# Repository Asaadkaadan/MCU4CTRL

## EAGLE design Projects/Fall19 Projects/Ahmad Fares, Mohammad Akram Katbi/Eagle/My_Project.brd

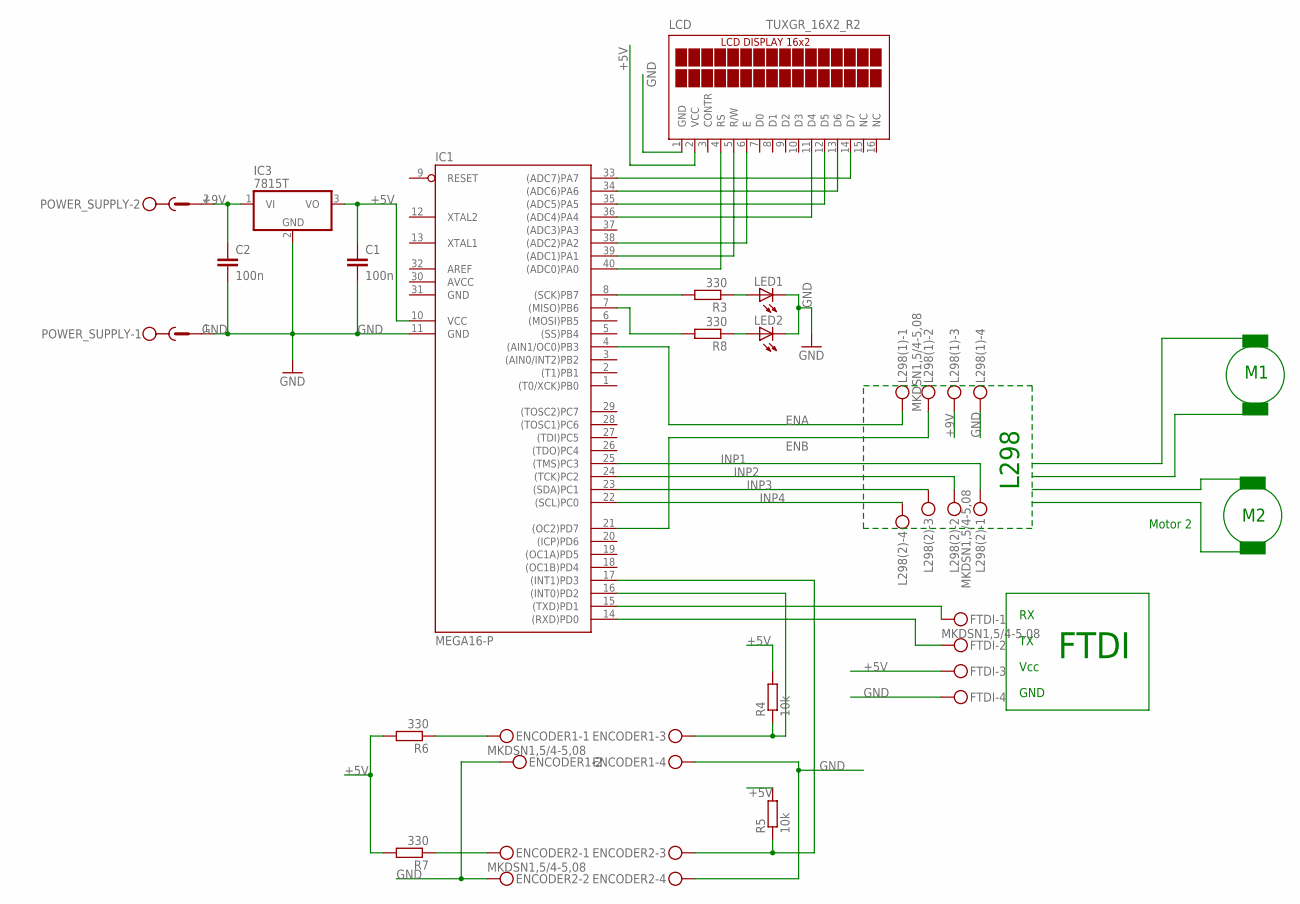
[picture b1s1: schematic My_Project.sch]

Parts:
C1, C2: 100n; C2.5-3
ENCODER1, ENCODER2: MKDSN1,5/4-5,08
FTDI: MKDSN1,5/4-5,08
IC1: MEGA16-P; DIL40; MPN ATMEGA16-16PU
IC3: 7815T; TO220H
L298(1), L298(2): MKDSN1,5/4-5,08
LCD: TUXGR_16X2_R2
LED1, LED2: LEDLZR181; LZR181
POWER_SUPPLY: MSTBV2
R3, R6, R7, R8: 330; 0207/10
R4, R5: 10k; 0207/10

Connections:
+5V: C1.1, FTDI.3, IC1.10 (VCC), IC3.3 (VO), LCD.2 (VCC), R4.2, R5.2, R6.2, R7.2
+9V: C2.1, IC3.1 (VI), L298(1).3, POWER_SUPPLY.2
AVCC: IC1.30 (AVCC)
ENA: IC1.4 ((AIN1/OC0)PB3), L298(1).1
ENB: IC1.21 ((OC2)PD7), L298(1).2
GND: C1.2, C2.2, ENCODER1.2, ENCODER1.4, ENCODER2.2, ENCODER2.4, FTDI.4, IC1.11 (GND), IC1.31 (GND), IC3.2 (GND), L298(1).4, LCD.1 (GND), LED1.K (C), LED2.K (C), POWER_SUPPLY.1
INP1: IC1.25 ((TMS)PC3), L298(2).1
INP2: IC1.24 ((TCK)PC2), L298(2).2
INP3: IC1.23 ((SDA)PC1), L298(2).3
INP4: IC1.22 ((SCL)PC0), L298(2).4
LCD(D4): IC1.36 ((ADC4)PA4), LCD.11 (D4)
LCD(D5): IC1.35 ((ADC5)PA5), LCD.12 (D5)
LCD(D6): IC1.34 ((ADC6)PA6), LCD.13 (D6)
LCD(D7): IC1.33 ((ADC7)PA7), LCD.14 (D7)
LCD(E): IC1.38 ((ADC2)PA2), LCD.6 (E)
LCD(RS): IC1.40 ((ADC0)PA0), LCD.4 (RS)
LCD(RW): IC1.39 ((ADC1)PA1), LCD.5 (R/W)
unnamed: IC1.7 ((MISO)PB6), R8.2
unnamed: IC1.8 ((SCK)PB7), R3.2
unnamed: LED1.A, R3.1
unnamed: LED2.A, R8.1
unnamed: ENCODER1.1, R6.1
unnamed: ENCODER1.3, IC1.16 ((INT0)PD2), R4.1
unnamed: ENCODER2.3, IC1.17 ((INT1)PD3), R5.1
unnamed: ENCODER2.1, R7.1
RX: FTDI.2, IC1.14 ((RXD)PD0)
TX: FTDI.1, IC1.15 ((TXD)PD1)

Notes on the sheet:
Vcc
GND
FTDI
Motor 2
L298

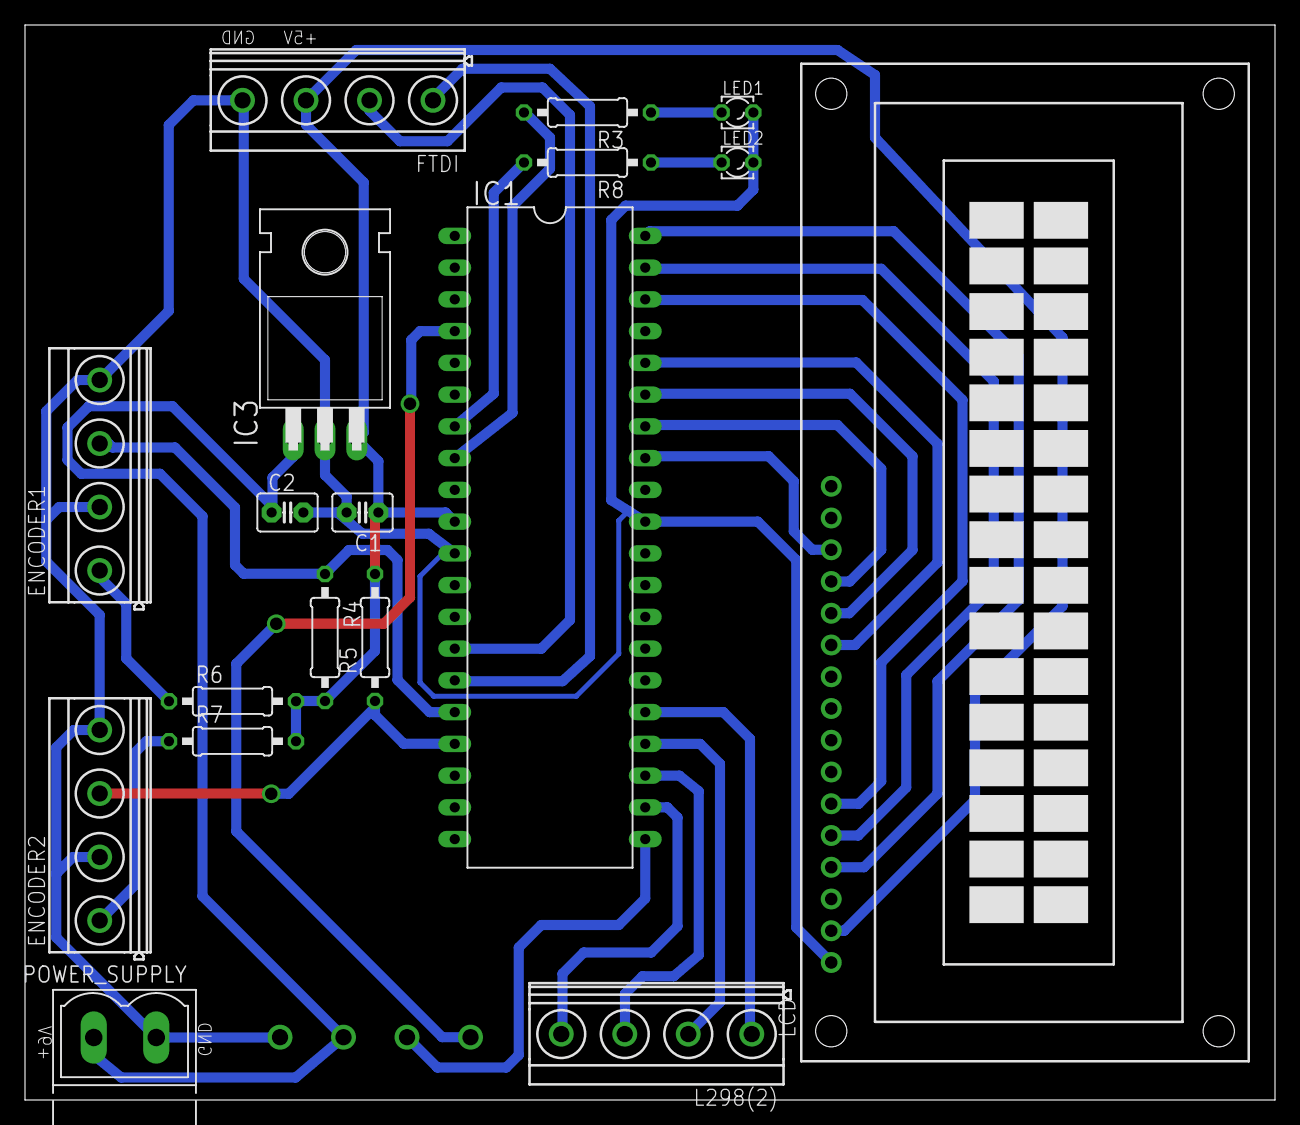
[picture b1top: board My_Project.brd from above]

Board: 2 copper layers, 100.0 x 86.0 mm, 19 parts (1 on the bottom side), 26 nets.

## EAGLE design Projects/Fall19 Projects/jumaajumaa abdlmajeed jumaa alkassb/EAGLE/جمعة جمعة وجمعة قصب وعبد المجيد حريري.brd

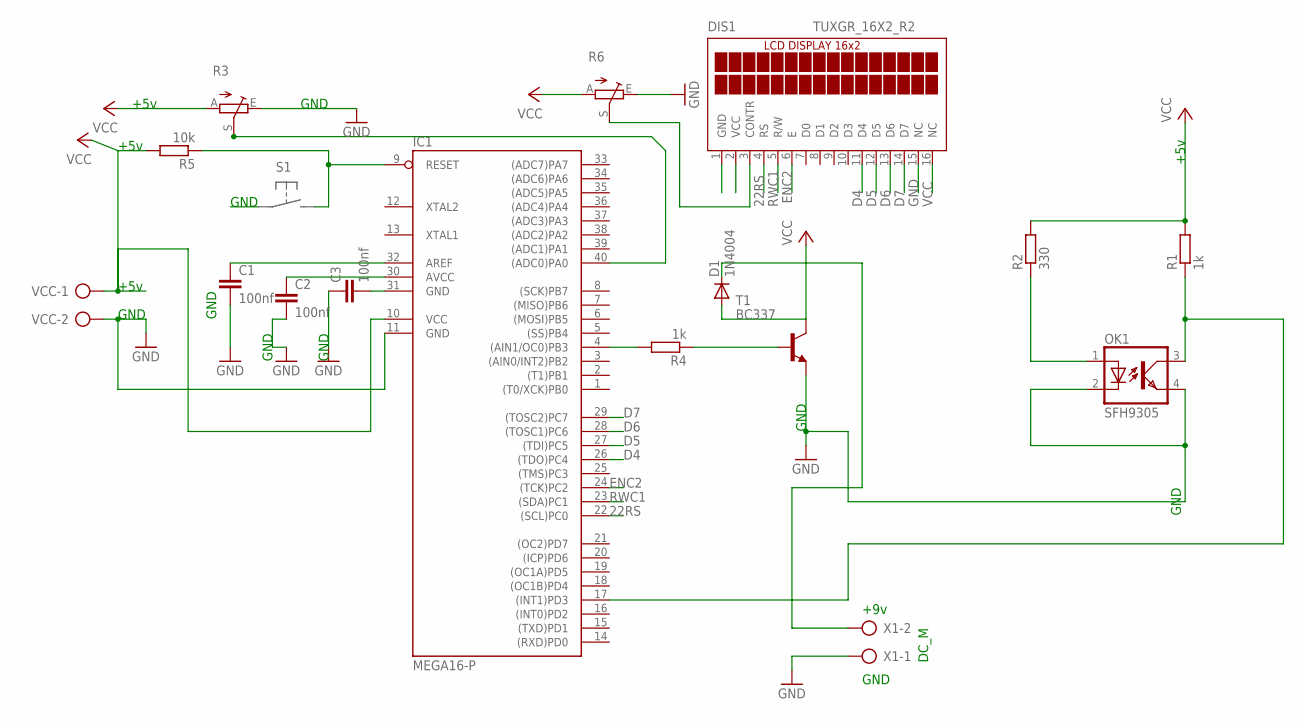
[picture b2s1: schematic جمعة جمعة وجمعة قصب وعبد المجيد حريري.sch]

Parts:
C1, C2, C3: 100nf; C2.5-3
D1: 1N4004; DO41-10
DIS1: TUXGR_16X2_R2
IC1: MEGA16-P; DIL40
OK1: SFH9305
R1, R4: 1k; 0204/7
R2: 330; 0204/7
R3, R6: TRIM_EU-CA9V; CA9V
R5: 10k; 0204/7
T1: BC337; TO92
VCC: AK300/2
X1: AK300/2

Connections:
22RS: DIS1.4 (RS), IC1.22 ((SCL)PC0)
D4: DIS1.11 (D4), IC1.26 ((TDO)PC4)
D5: DIS1.12 (D5), IC1.27 ((TDI)PC5)
D6: DIS1.13 (D6), IC1.28 ((TOSC1)PC6)
D7: DIS1.14 (D7), IC1.29 ((TOSC2)PC7)
ENC2: DIS1.6 (E), IC1.24 ((TCK)PC2)
GND: C1.2, C2.2, C3.1, DIS1.15 (NC), IC1.11 (GND), OK1.2 (C), OK1.4 (EMIT), R3.E, R6.E, T1.1 (E), VCC.2, X1.1
unnamed: OK1.1 (A), R2.1
unnamed: IC1.17 ((INT1)PD3), OK1.3 (COL), R1.1
unnamed: IC1.9 (RESET), R5.1
unnamed: C1.1, IC1.32 (AREF)
unnamed: R4.1, T1.2 (B)
unnamed: IC1.4 ((AIN1/OC0)PB3), R4.2
unnamed: C2.1, IC1.30 (AVCC)
unnamed: C3.2, IC1.31 (GND)
unnamed: IC1.40 ((ADC0)PA0), R3.S
unnamed: DIS1.3 (CONTR), R6.S
unnamed: D1.A, T1.3 (C)
RWC1: DIS1.5 (R/W), IC1.23 ((SDA)PC1)
VCC: D1.C, DIS1.16 (NC), IC1.10 (VCC), R1.2, R2.2, R3.A, R5.2, R6.A, VCC.1, X1.2

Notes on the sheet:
+5v
GND
DC_M
+9v

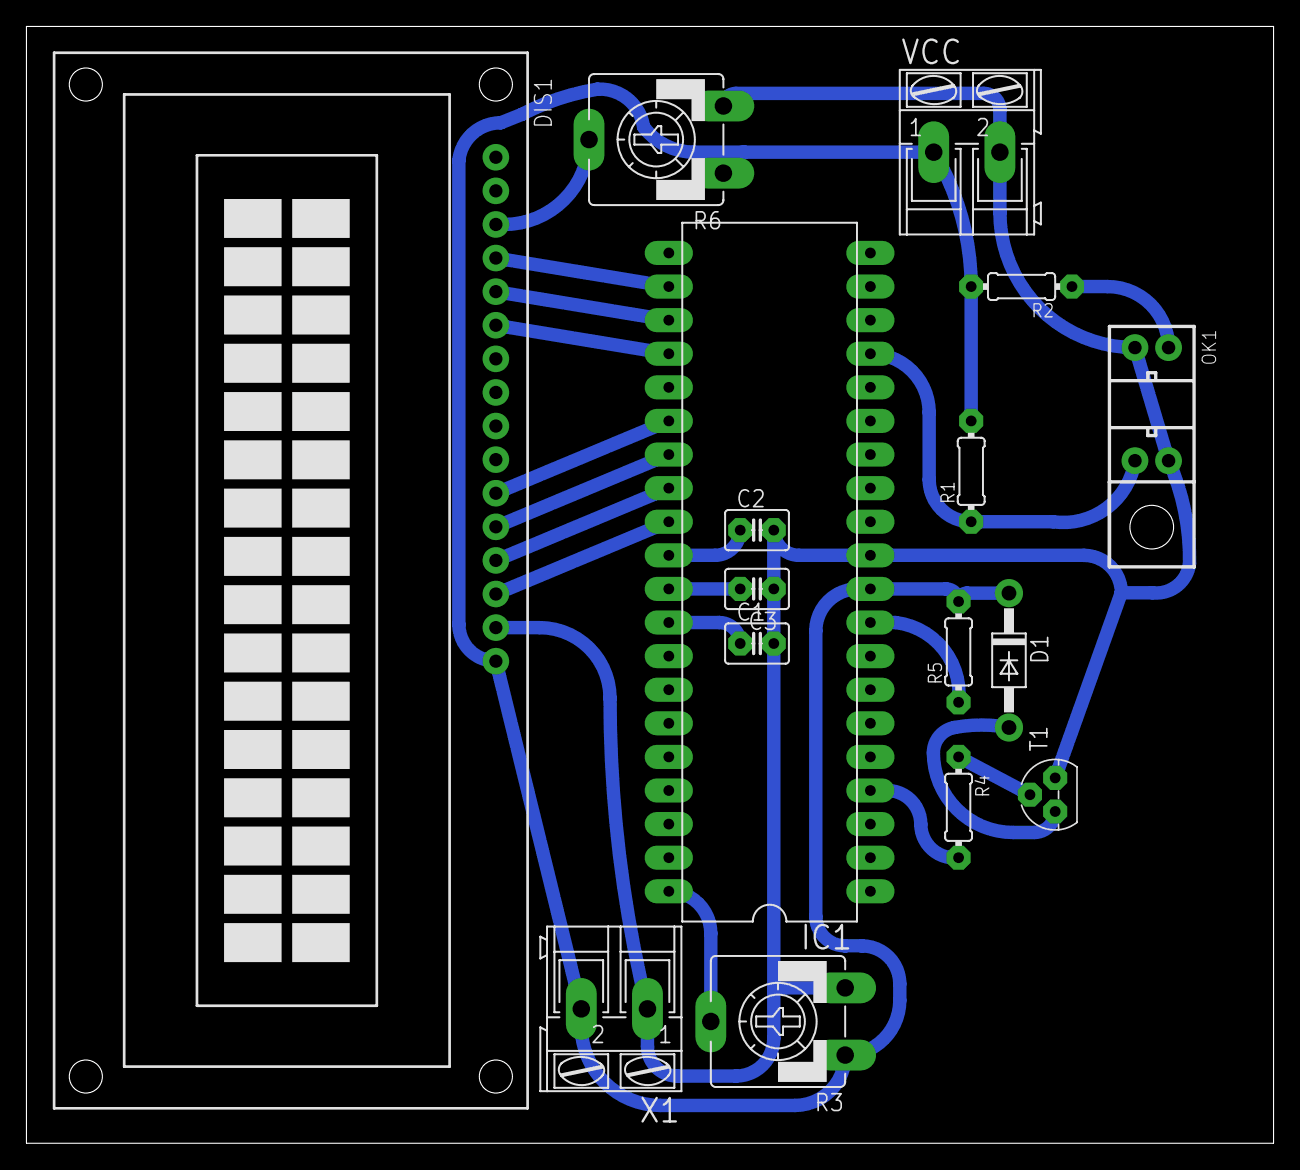
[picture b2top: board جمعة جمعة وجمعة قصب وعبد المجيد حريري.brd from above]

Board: 2 copper layers, 94.3 x 84.4 mm, 16 parts (0 on the bottom side), 20 nets.

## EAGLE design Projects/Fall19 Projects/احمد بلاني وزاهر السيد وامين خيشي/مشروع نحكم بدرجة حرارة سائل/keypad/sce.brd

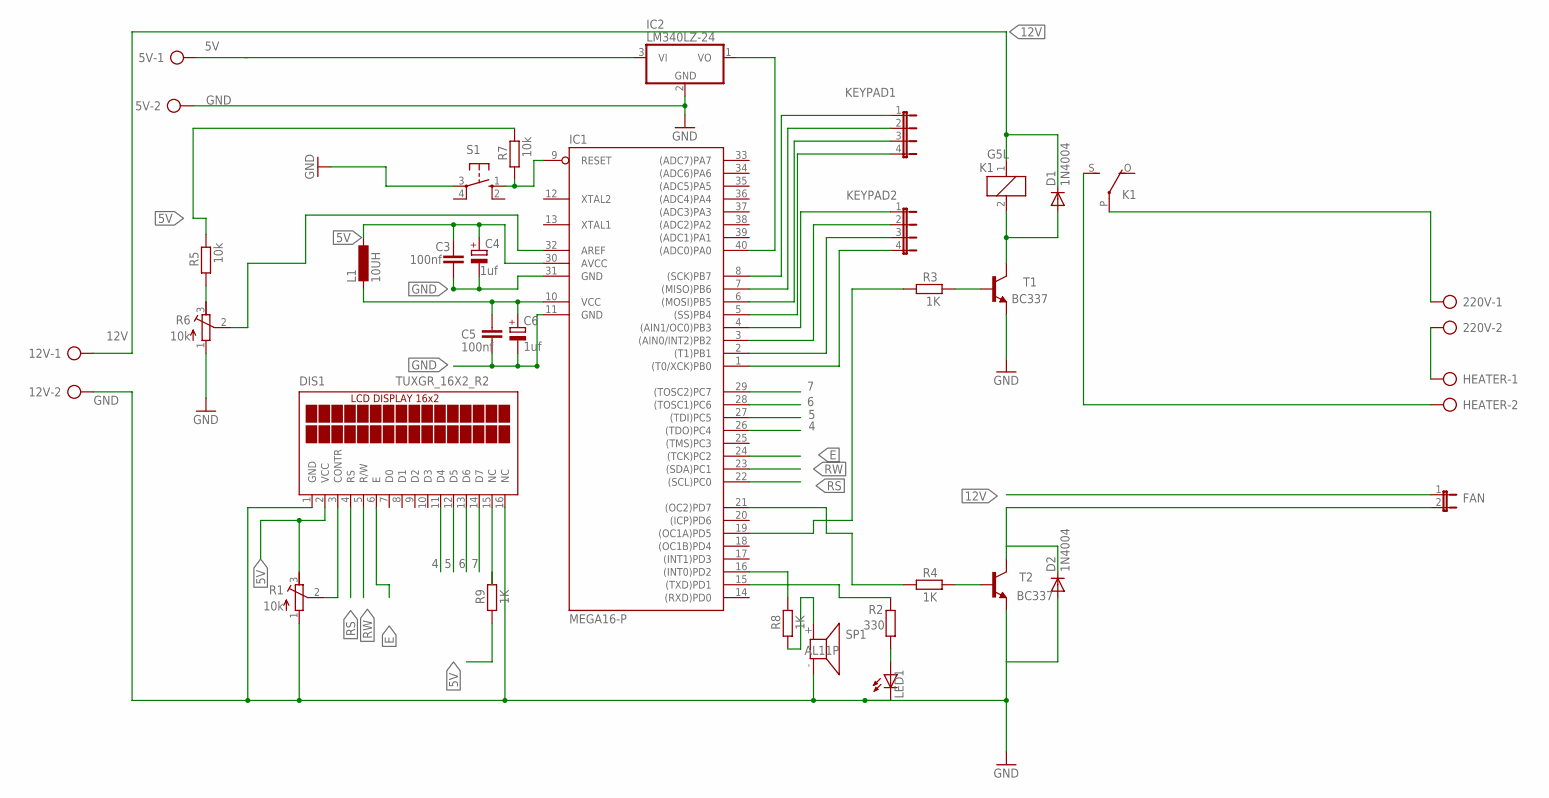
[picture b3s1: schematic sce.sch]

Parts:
5V, 12V, 220V: AK500/2
C3, C5: 100nf; C025-025X050
C4, C6: 1uf; E2,5-5
D1, D2: 1N4004; DO41-10
DIS1: TUXGR_16X2_R2
FAN: JP1E; JP1
HEATER: AK500/2
IC1: MEGA16-P; DIL40
IC2: LM340LZ-24; TO92
K1: G5L; G5LE
KEYPAD1, KEYPAD2: JP4E; JP4
L1: 10UH; 6000-XXXX-RC
LED1: LED5MM
R1, R6: 10k; RTRIM3339P
R2: 330; 0207/10
R3, R4, R8, R9: 1K; 0207/10
R5, R7: 10k; 0207/10
S1: 10-XX; B3F-10XX
SP1: AL11P
T1, T2: BC337; TO92

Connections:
1: C5.1, C6.+, IC1.10 (VCC), L1.2
4: DIS1.11 (D4), IC1.26 ((TDO)PC4)
5: DIS1.12 (D5), IC1.27 ((TDI)PC5)
5V: 5V.1, C3.1, C4.+, DIS1.2 (VCC), IC1.30 (AVCC), IC2.3 (VI), L1.1, R1.3 (E), R5.2, R7.2, R9.1
6: DIS1.13 (D6), IC1.28 ((TOSC1)PC6)
7: DIS1.14 (D7), IC1.29 ((TOSC2)PC7)
12V: 12V.1, D1.C, FAN.1, K1.1
E: DIS1.6 (E), IC1.24 ((TCK)PC2)
GND: 5V.2, 12V.2, C3.2, C4.-, C5.2, C6.-, D2.A, DIS1.1 (GND), DIS1.16 (NC), IC1.11 (GND), IC1.31 (GND), IC2.2 (GND), LED1.K (C), R1.1 (A), R6.1 (A), SP1.- (1), T1.1 (E), T2.1 (E)
HOT: IC1.40 ((ADC0)PA0), IC2.1 (VO)
KEYPAD2: IC1.1 ((T0/XCK)PB0), KEYPAD2.4
unnamed: IC1.9 (RESET), R7.1, S1.1 (S)
unnamed: R4.2, T2.2 (B)
unnamed: R3.2, T1.2 (B)
unnamed: IC1.21 ((OC2)PD7), R4.1
unnamed: IC1.3 ((AIN0/INT2)PB2), KEYPAD2.2
unnamed: IC1.19 ((OC1A)PD5), R3.1
unnamed: D1.A, K1.2, T1.3 (C)
unnamed: IC1.5 ((SS)PB4), KEYPAD1.4
unnamed: 220V.1, K1.P
unnamed: 220V.2, HEATER.1
unnamed: IC1.16 ((INT0)PD2), R8.2
unnamed: IC1.2 ((T1)PB1), KEYPAD2.3
unnamed: HEATER.2, K1.S
unnamed: IC1.4 ((AIN1/OC0)PB3), KEYPAD2.1
unnamed: D2.C, FAN.2, T2.3 (C)
unnamed: IC1.15 ((TXD)PD1), R2.2
unnamed: DIS1.3 (CONTR), R1.2 (S)
unnamed: IC1.6 ((MOSI)PB5), KEYPAD1.3
unnamed: LED1.A, R2.1
unnamed: IC1.7 ((MISO)PB6), KEYPAD1.2
unnamed: R8.1, SP1.+ (2)
unnamed: IC1.8 ((SCK)PB7), KEYPAD1.1
unnamed: IC1.32 (AREF), R6.2 (S)
unnamed: R5.1, R6.3 (E)
RS: DIS1.4 (RS), IC1.22 ((SCL)PC0)
RW: DIS1.5 (R/W), IC1.23 ((SDA)PC1)

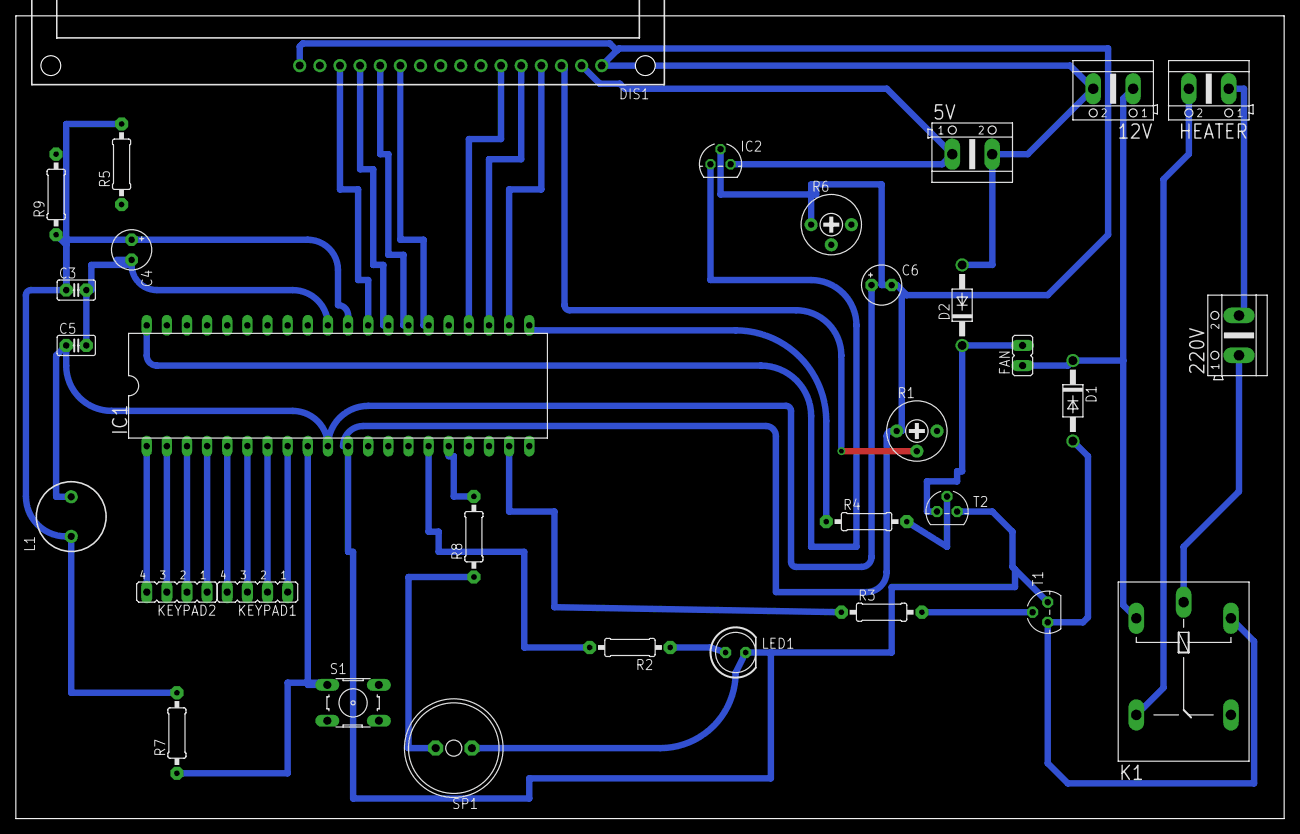
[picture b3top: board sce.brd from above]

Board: 2 copper layers, 160.0 x 101.3 mm, 32 parts (0 on the bottom side), 37 nets.

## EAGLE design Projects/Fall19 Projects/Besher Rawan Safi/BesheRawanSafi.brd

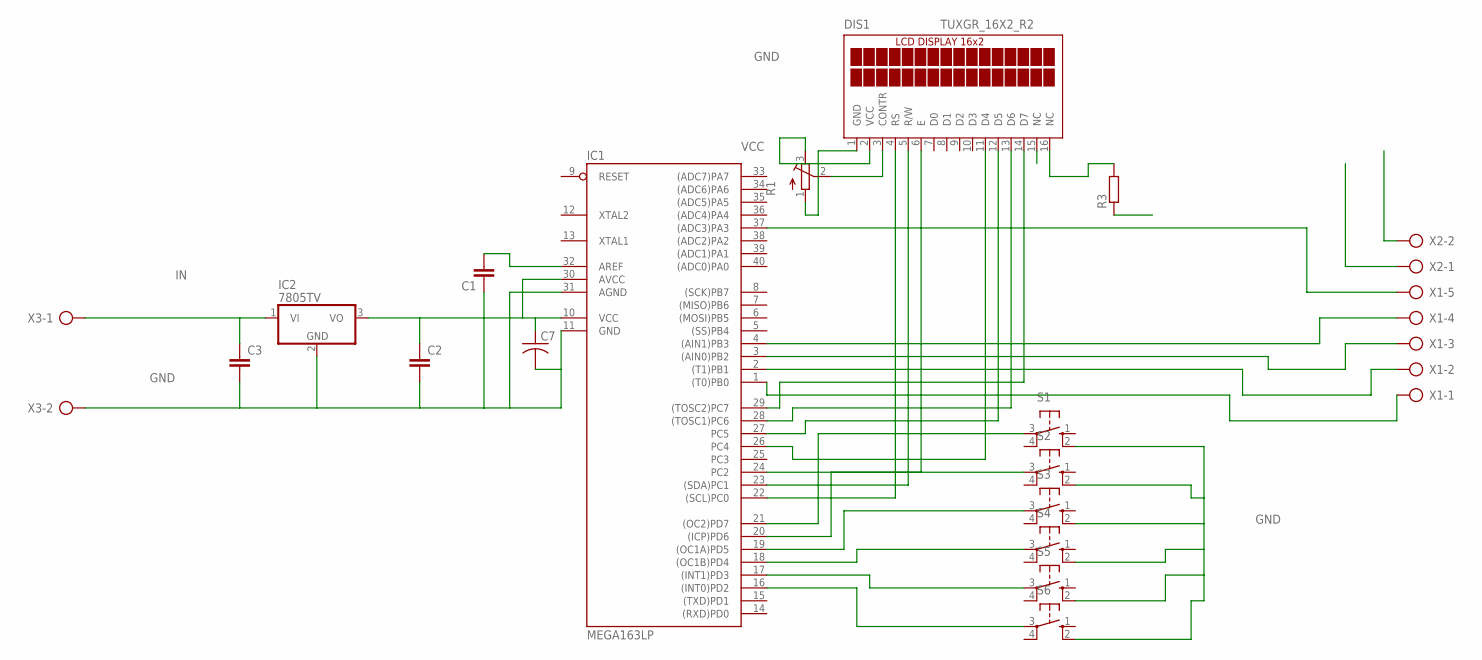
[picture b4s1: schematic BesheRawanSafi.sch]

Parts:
C1, C2, C3: C5/3; C5B3
C7: C-US050-035X075; C050-035X075
DIS1: TUXGR_16X2_R2
IC1: MEGA163LP; DIL40
IC2: 7805TV; TO220V
R1: R-TRIMM64X; RTRIM64X
R3: R-EU_0207/7; 0207/7
S1, S2, S3, S4, S5, S6: 10-XX; B3F-10XX
X1: AK500/5-H
X2: AK500/2-H
X3: AK300/2

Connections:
ASDASD: DIS1.16 (NC), R3.2
GND: C1.1, C2.2, C3.2, C7.2, DIS1.1 (GND), IC1.11 (GND), IC1.31 (AGND), IC2.2 (GND), R1.1 (E), R3.1, S1.2 (S1), S2.2 (S1), S3.2 (S1), S4.2 (S1), S5.2 (S1), S6.2 (S1), X2.1, X3.2
IN: C3.1, IC2.1 (VI), X3.1
unnamed: IC1.1 ((T0)PB0), X1.1
unnamed: IC1.2 ((T1)PB1), X1.2
unnamed: C1.2, IC1.32 (AREF)
unnamed: IC1.3 ((AIN0)PB2), X1.3
unnamed: IC1.4 ((AIN1)PB3), X1.4
unnamed: DIS1.13 (D6), IC1.28 ((TOSC1)PC6)
unnamed: DIS1.14 (D7), IC1.29 ((TOSC2)PC7)
unnamed: DIS1.12 (D5), IC1.27 (PC5)
unnamed: DIS1.11 (D4), IC1.26 (PC4)
unnamed: IC1.37 ((ADC3)PA3), X1.5
unnamed: DIS1.4 (RS), IC1.22 ((SCL)PC0)
unnamed: DIS1.5 (R/W), IC1.23 ((SDA)PC1)
unnamed: DIS1.6 (E), IC1.24 (PC2)
unnamed: DIS1.3 (CONTR), R1.2 (S)
unnamed: IC1.21 ((OC2)PD7), S1.3
unnamed: IC1.20 ((ICP)PD6), S2.3
unnamed: IC1.19 ((OC1A)PD5), S3.3
unnamed: IC1.18 ((OC1B)PD4), S4.3
unnamed: IC1.17 ((INT1)PD3), S5.3
unnamed: IC1.16 ((INT0)PD2), S6.3
VCC: C2.1, C7.1, DIS1.2 (VCC), DIS1.15 (NC), IC1.10 (VCC), IC1.30 (AVCC), IC2.3 (VO), R1.3 (A), X2.2

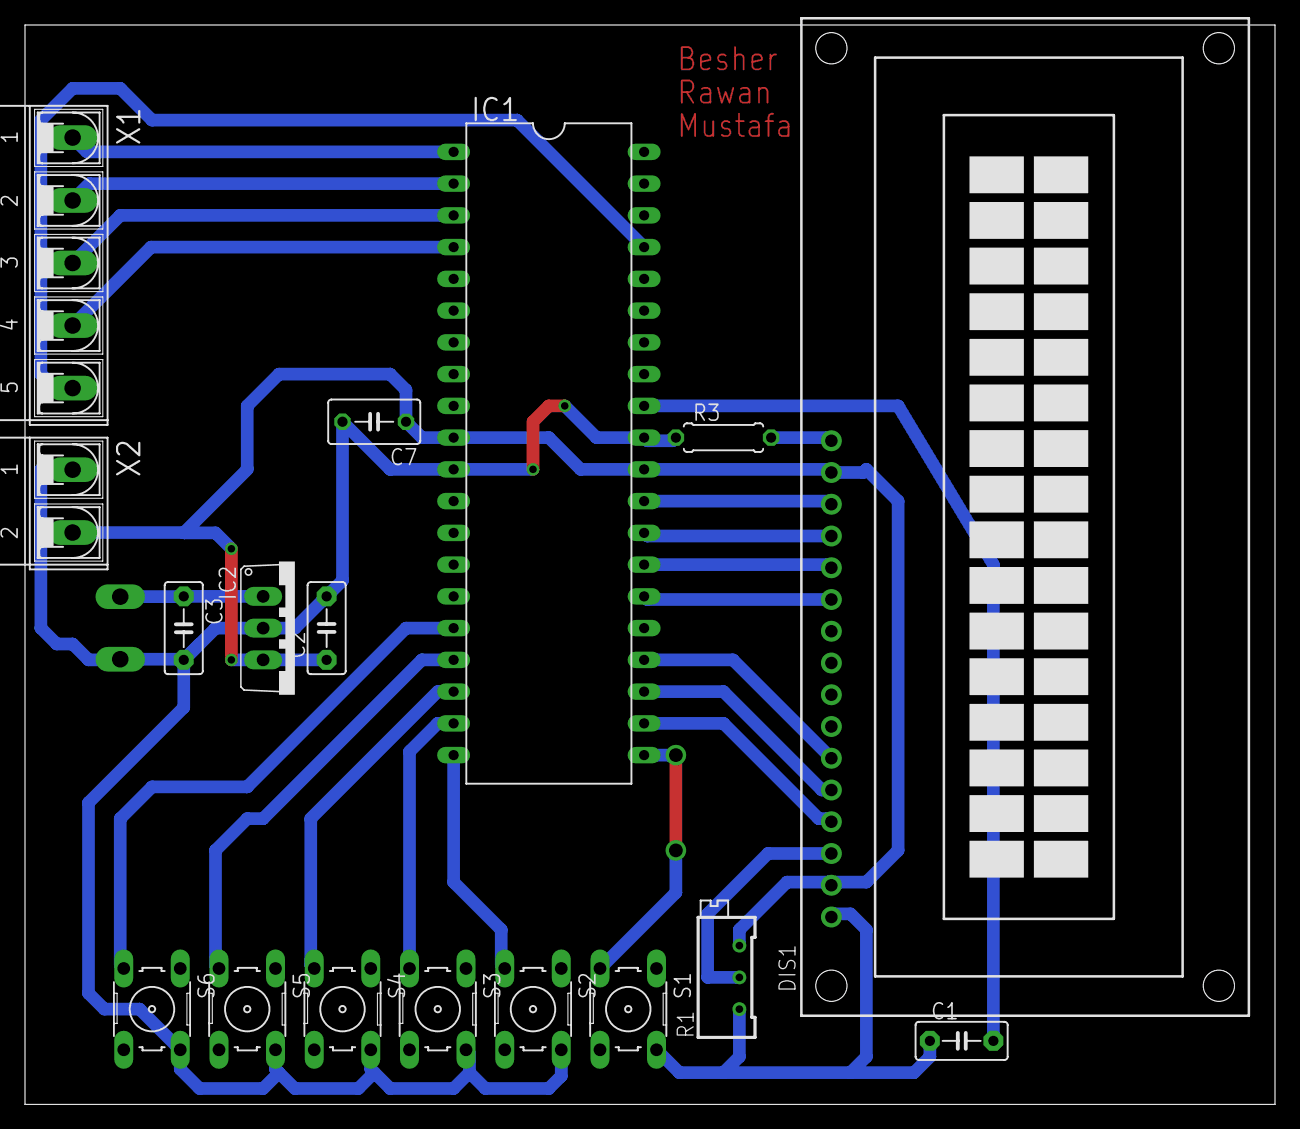
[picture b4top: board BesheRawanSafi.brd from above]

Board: 2 copper layers, 100.0 x 86.3 mm, 18 parts (1 on the bottom side), 24 nets.

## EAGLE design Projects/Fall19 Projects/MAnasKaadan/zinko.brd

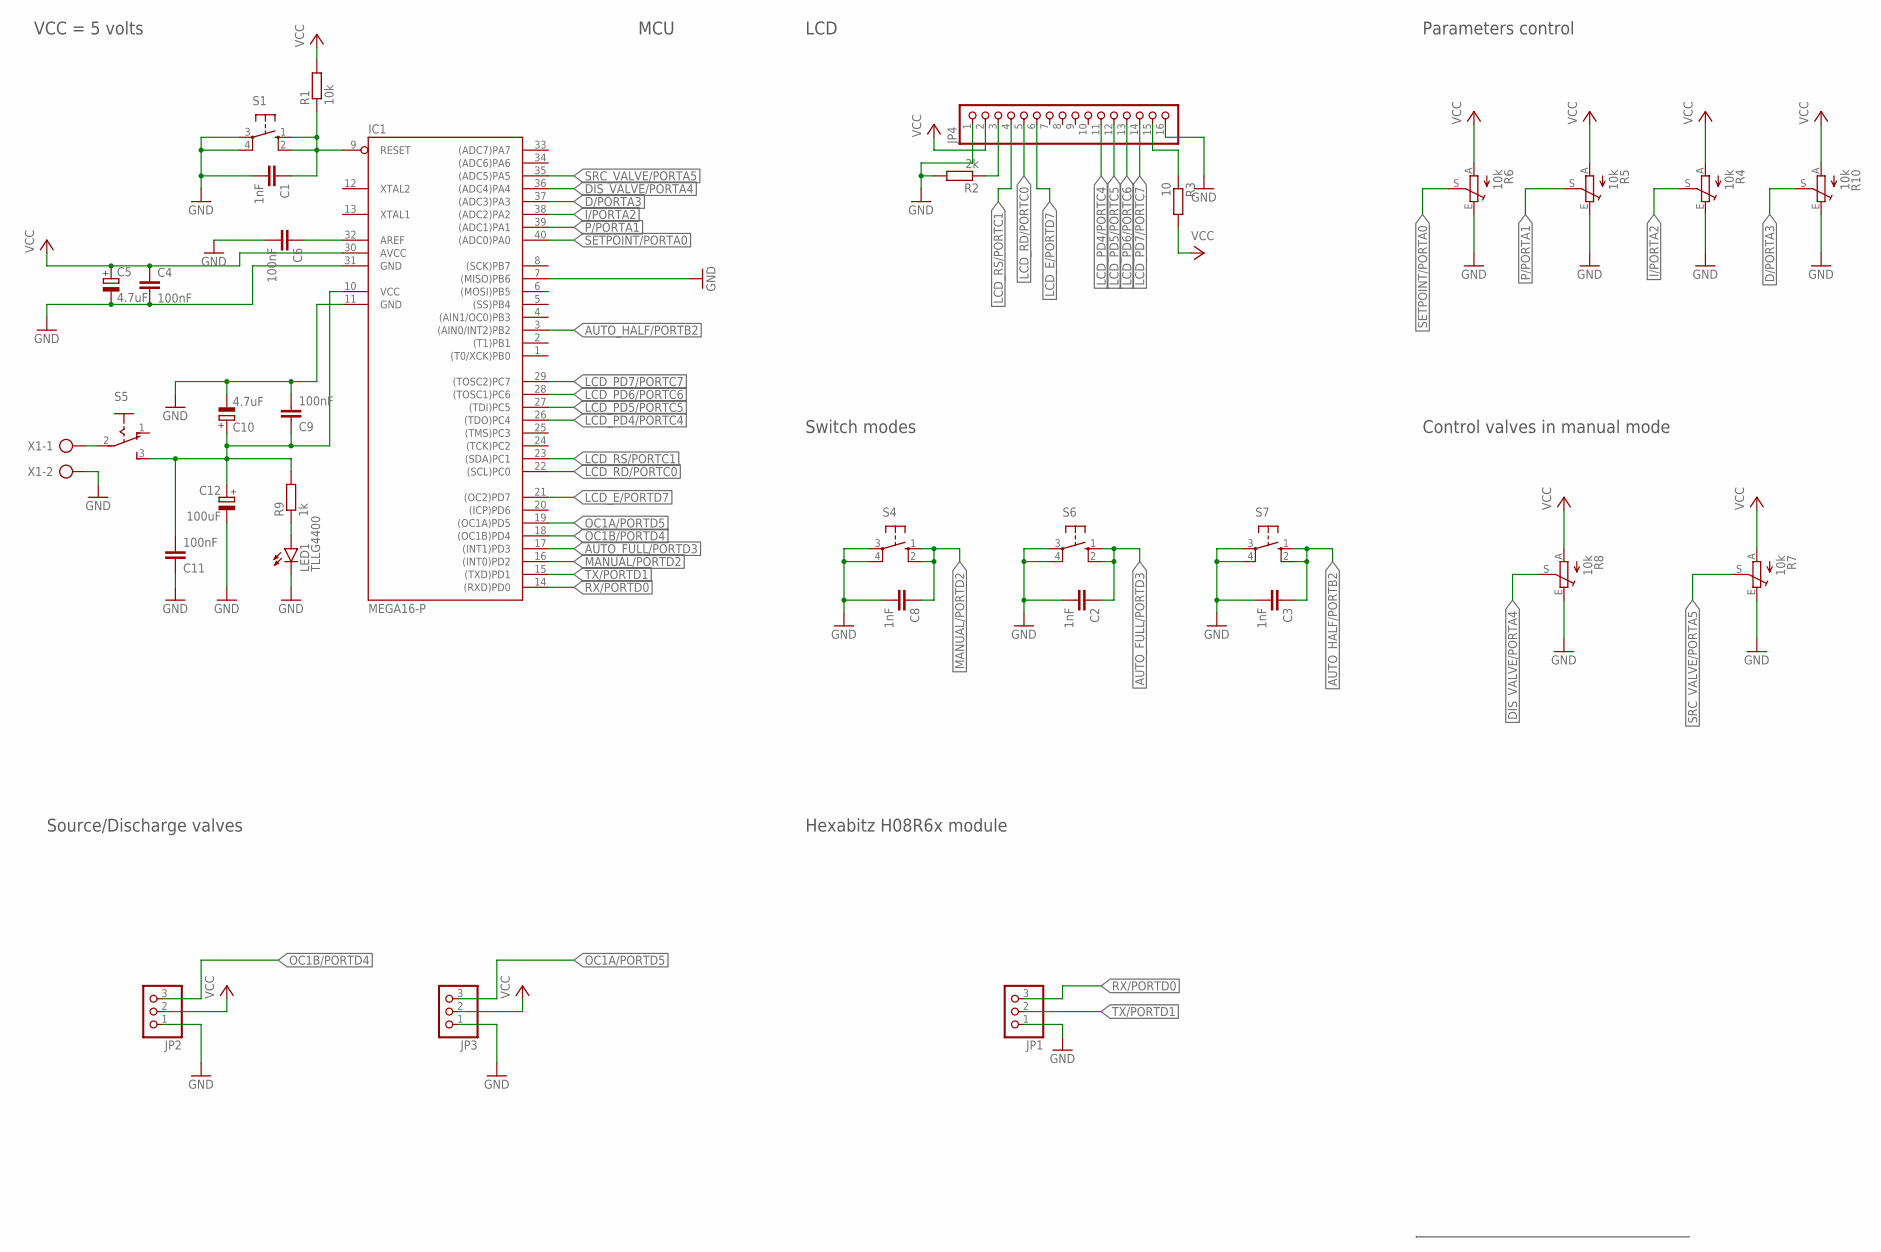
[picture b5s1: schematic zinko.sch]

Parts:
C1, C2, C3, C8: 1nF; C025-024X044
C4, C6, C9, C11: 100nF; C025-024X044
C5: 4.7uF; E2,5-6E
C10: 4.7uF; B45181A
C12: 100uF; B45181A
IC1: MEGA16-P; DIL40
JP1, JP2, JP3: PINHD-1X3; 1X03
JP4: PINHD-1X16; 1X16
LED1: TLLG4400; LED3MM
R1: 10k; 0204/7
R2: 2k; 0204/7
R3: 10; 0204/7
R4, R5, R6, R7, R8, R10: 10k; RJ9W
R9: 1k; 0204/7
S1, S4, S6, S7: 10-XX; B3F-10XX
S5: 255SB
X1: AK300/2

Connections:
AUTO_FULL/PORTD3: C2.1, IC1.17 ((INT1)PD3), S6.1 (S), S6.2 (S1)
AUTO_HALF/PORTB2: C3.1, IC1.3 ((AIN0/INT2)PB2), S7.1 (S), S7.2 (S1)
D/PORTA3: IC1.37 ((ADC3)PA3), R10.S
DIS_VALVE/PORTA4: IC1.36 ((ADC4)PA4), R8.S
GND: C1.2, C2.2, C3.2, C4.2, C5.-, C6.2, C8.2, C9.2, C10.-, C11.1, C12.-, IC1.7 ((MISO)PB6), IC1.11 (GND), IC1.31 (GND), JP1.1, JP2.1, JP3.1, JP4.1, JP4.16, LED1.K (C), R2.2, R4.E, R5.E, R6.E, R7.E, R8.E, R10.E, S1.3, S1.4 (P1), S4.3, S4.4 (P1), S6.3, S6.4 (P1), S7.3, S7.4 (P1), X1.2
I/PORTA2: IC1.38 ((ADC2)PA2), R4.S
LCD_E/PORTD7: IC1.21 ((OC2)PD7), JP4.6
LCD_PD4/PORTC4: IC1.26 ((TDO)PC4), JP4.11
LCD_PD5/PORTC5: IC1.27 ((TDI)PC5), JP4.12
LCD_PD6/PORTC6: IC1.28 ((TOSC1)PC6), JP4.13
LCD_PD7/PORTC7: IC1.29 ((TOSC2)PC7), JP4.14
LCD_RD/PORTC0: IC1.22 ((SCL)PC0), JP4.5
LCD_RS/PORTC1: IC1.23 ((SDA)PC1), JP4.4
MANUAL/PORTD2: C8.1, IC1.16 ((INT0)PD2), S4.1 (S), S4.2 (S1)
unnamed: C1.1, IC1.9 (RESET), R1.1, S1.1 (S), S1.2 (S1)
unnamed: JP4.15, R3.1
unnamed: C6.1, IC1.32 (AREF)
unnamed: JP4.3, R2.1
unnamed: S5.2, X1.1
unnamed: LED1.A, R9.1
OC1A/PORTD5: IC1.19 ((OC1A)PD5), JP3.3
OC1B/PORTD4: IC1.18 ((OC1B)PD4), JP2.3
P/PORTA1: IC1.39 ((ADC1)PA1), R5.S
RX/PORTD0: IC1.14 ((RXD)PD0), JP1.3
SETPOINT/PORTA0: IC1.40 ((ADC0)PA0), R6.S
SRC_VALVE/PORTA5: IC1.35 ((ADC5)PA5), R7.S
TX/PORTD1: IC1.15 ((TXD)PD1), JP1.2
VCC: C4.1, C5.+, C9.1, C10.+, C11.2, C12.+, IC1.10 (VCC), IC1.30 (AVCC), JP2.2, JP3.2, JP4.2, R1.2, R3.2, R4.A, R5.A, R6.A, R7.A, R8.A, R9.2, R10.A, S5.3 (S)

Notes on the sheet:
VCC = 5 volts
MCU
LCD
Parameters control
Switch modes
Hexabitz H08R6x module
Source/Discharge valves
Control valves in manual mode

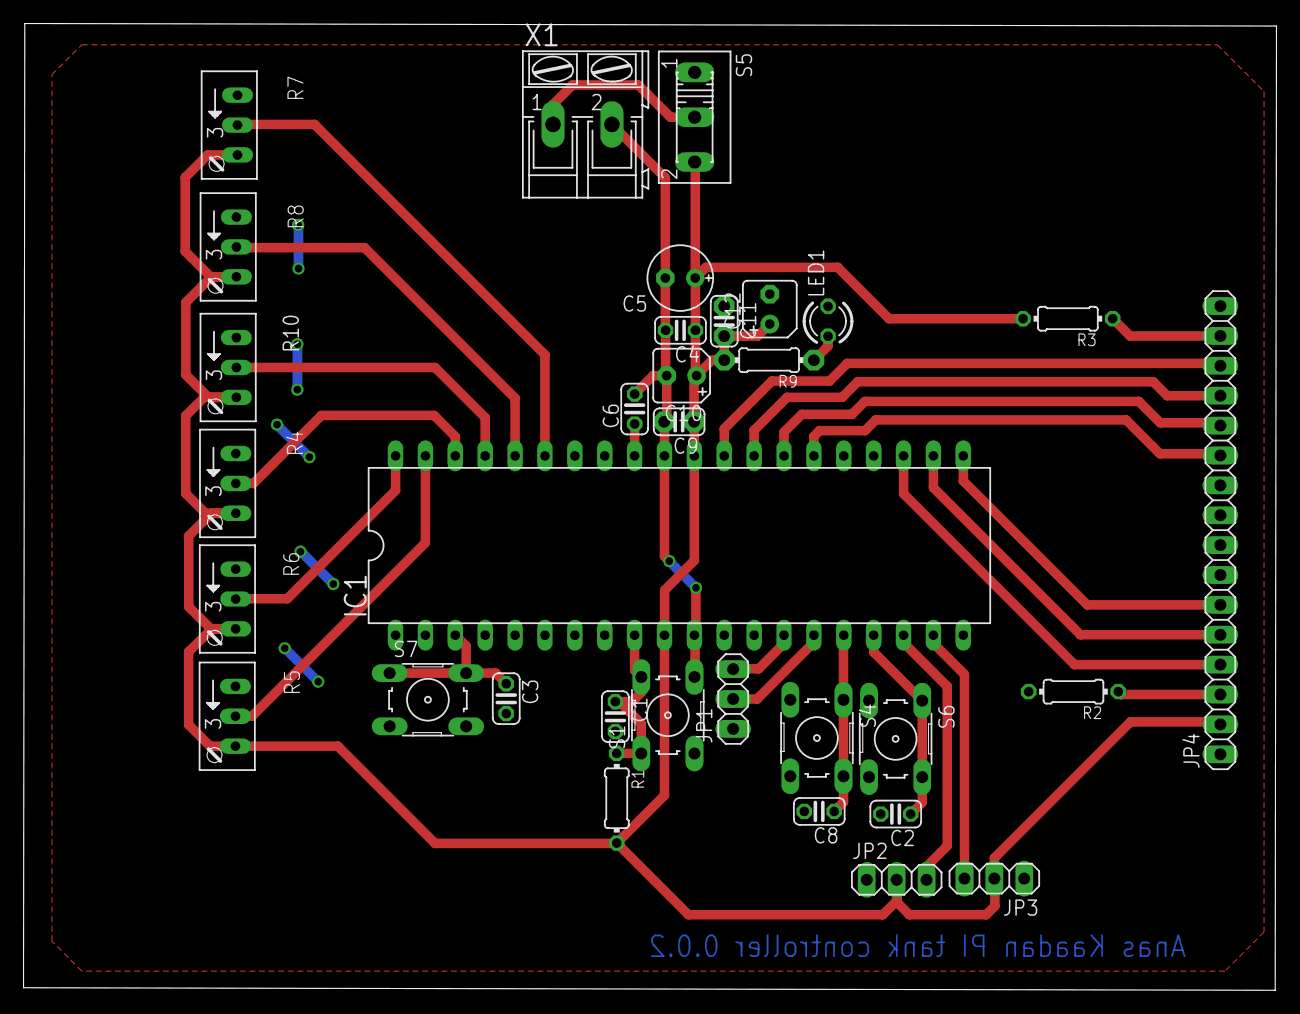
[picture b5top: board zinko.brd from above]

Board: 2 copper layers, 106.5 x 82.2 mm, 33 parts (0 on the bottom side), 28 nets.

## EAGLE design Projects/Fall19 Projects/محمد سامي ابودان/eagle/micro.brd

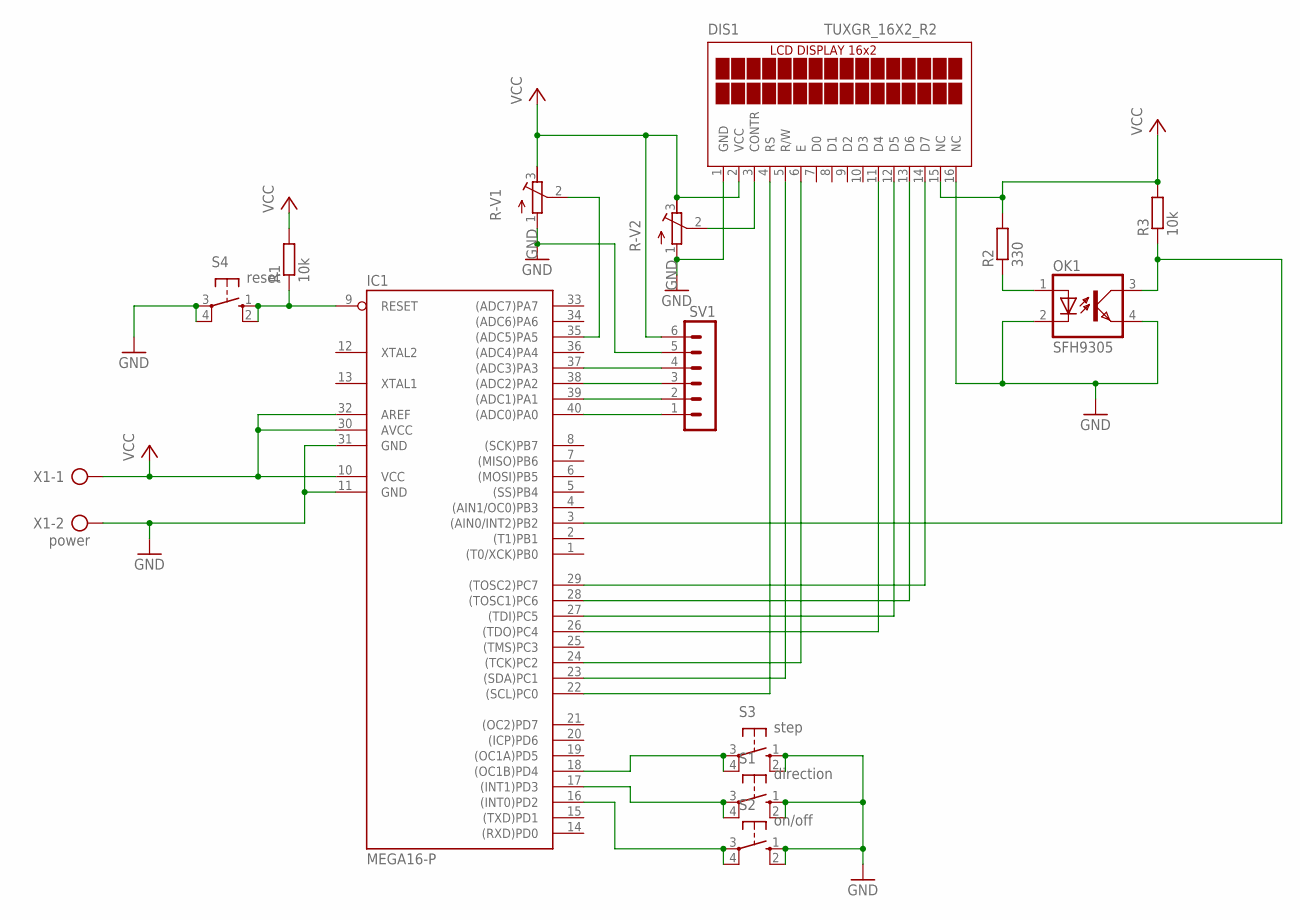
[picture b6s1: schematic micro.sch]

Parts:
DIS1: TUXGR_16X2_R2
IC1: MEGA16-P; DIL40
OK1: SFH9305
R1, R3: 10k; 0204/5
R2: 330; 0204/5
R-V1, R-V2: R-V
S1: direction; B3F-10XX
S2: on/off; B3F-10XX
S3: step; B3F-10XX
S4: reset; B3F-10XX
SV1: MA06-1
X1: power; AK300/2

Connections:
GND: DIS1.1 (GND), DIS1.16 (NC), IC1.11 (GND), IC1.31 (GND), OK1.2 (C), OK1.4 (EMIT), R-V1.1 (A), R-V2.1 (A), S1.1 (S), S1.2 (S1), S2.1 (S), S2.2 (S1), S3.1 (S), S3.2 (S1), S4.3, S4.4 (P1), SV1.5, X1.2
unnamed: DIS1.14 (D7), IC1.29 ((TOSC2)PC7)
unnamed: DIS1.13 (D6), IC1.28 ((TOSC1)PC6)
unnamed: DIS1.12 (D5), IC1.27 ((TDI)PC5)
unnamed: DIS1.11 (D4), IC1.26 ((TDO)PC4)
unnamed: DIS1.6 (E), IC1.24 ((TCK)PC2)
unnamed: DIS1.4 (RS), IC1.22 ((SCL)PC0)
unnamed: DIS1.3 (CONTR), R-V2.2 (S)
unnamed: IC1.3 ((AIN0/INT2)PB2), OK1.3 (COL), R3.1
unnamed: IC1.35 ((ADC5)PA5), R-V1.2 (S)
unnamed: DIS1.5 (R/W), IC1.23 ((SDA)PC1)
unnamed: IC1.40 ((ADC0)PA0), SV1.1
unnamed: IC1.39 ((ADC1)PA1), SV1.2
unnamed: IC1.38 ((ADC2)PA2), SV1.3
unnamed: IC1.17 ((INT1)PD3), S1.3, S1.4 (P1)
unnamed: IC1.37 ((ADC3)PA3), SV1.4
unnamed: IC1.16 ((INT0)PD2), S2.3, S2.4 (P1)
unnamed: IC1.18 ((OC1B)PD4), S3.3, S3.4 (P1)
unnamed: OK1.1 (A), R2.1
unnamed: IC1.9 (RESET), R1.1, S4.1 (S), S4.2 (S1)
VCC: DIS1.2 (VCC), DIS1.15 (NC), IC1.10 (VCC), IC1.30 (AVCC), IC1.32 (AREF), R1.2, R2.2, R3.2, R-V1.3 (E), R-V2.3 (E), SV1.6, X1.1

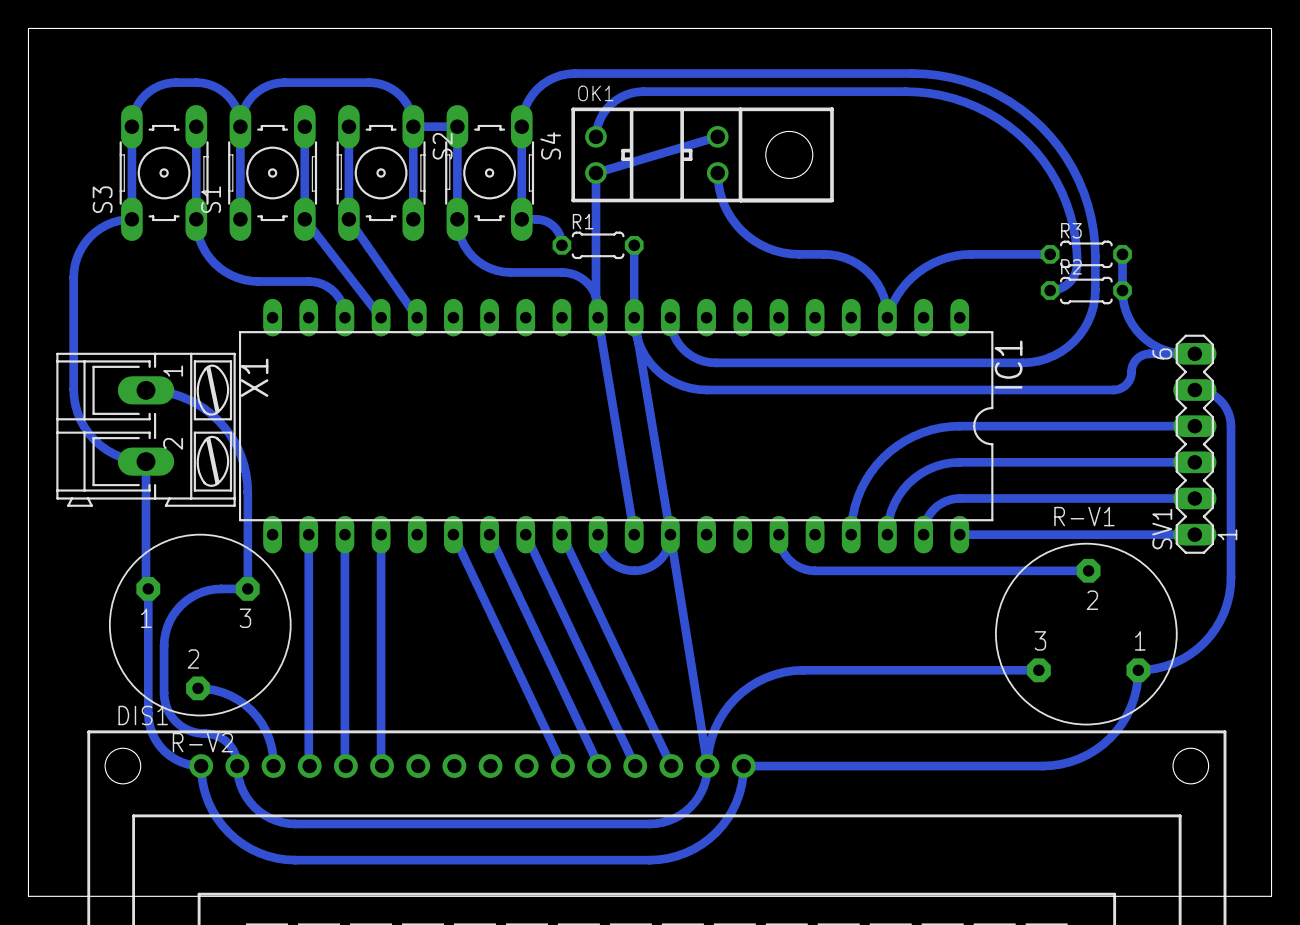
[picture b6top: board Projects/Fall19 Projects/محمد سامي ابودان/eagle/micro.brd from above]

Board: 2 copper layers, 87.3 x 61.0 mm, 14 parts (0 on the bottom side), 21 nets.

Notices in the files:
parts and their libraries:
schule_xl: © by Ralf Stutzenberger
